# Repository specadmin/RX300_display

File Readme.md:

# Lexus RX300 LCD Display with Rear/Side Cameras View and Multimedia Support #

This project is an LCD display for Lexus RX300 (1998...2003). It is beeing built in order to replace the standard "blue" display in Lexus RX300 and Toyota Harrier.

<div align="center">  </div>
<div align="center">  </div>

----

For now this project has:

+ a complete integration with vehicle's MPX bus;
+ a complete integration with climate control and trip computer;
+ up to three analog cameras support (composite input);
+ close-to-original display view (any view can be built);
+ real time clock.

The following tasks are in progress:

* on-board player support (amplifier, radio and CD-player);
* migrating to ARM STM32 platform.

The following features could be implemented in future:

* HDMI input for Android-stick;
* independent media center with full-band radio and MP3 support.

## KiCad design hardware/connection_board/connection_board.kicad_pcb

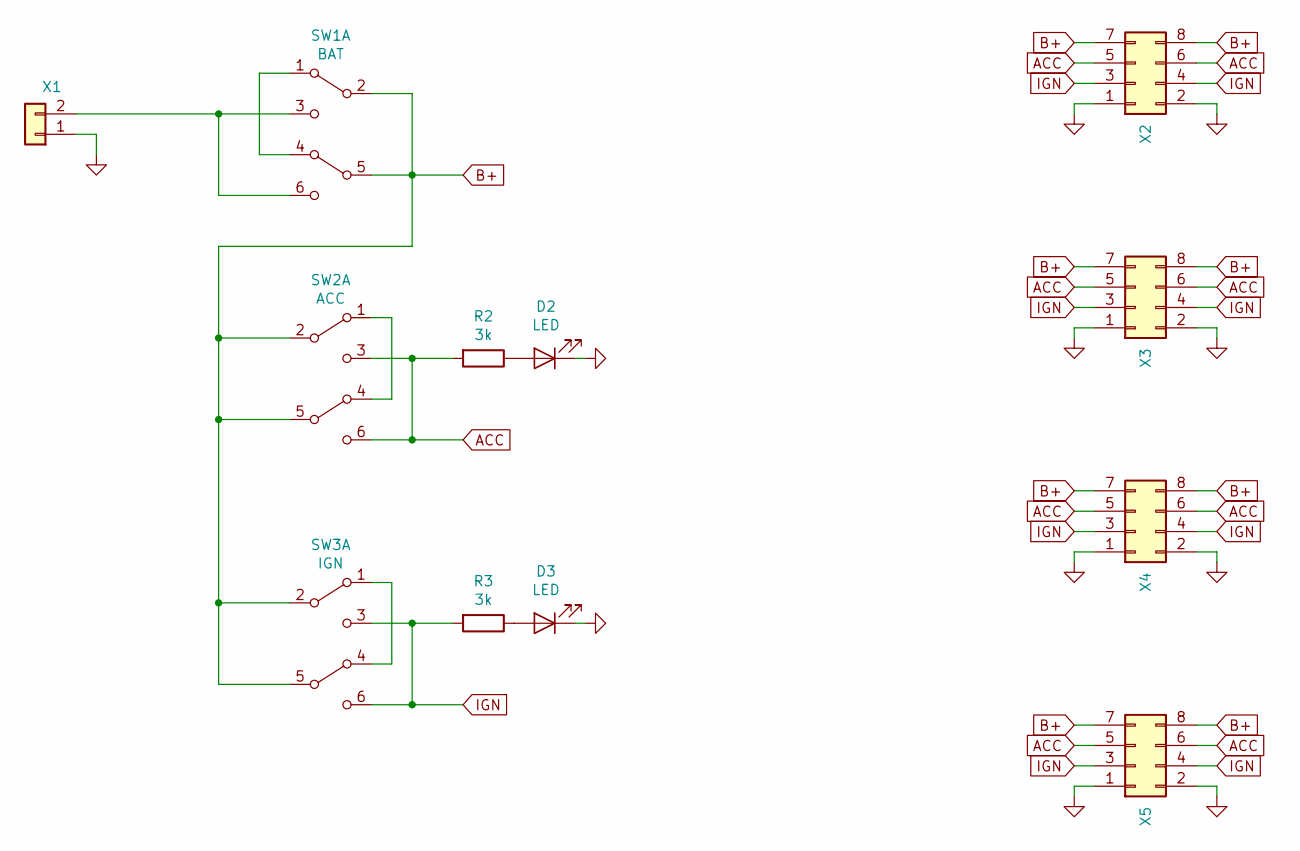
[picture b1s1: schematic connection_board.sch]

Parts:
D2, D3: LED; LED_D3.0mm
R2, R3: 3k; R_0805_2012Metric
SW1: BAT; Switch_2x03
SW2: ACC; Switch_2x03
SW3: IGN; Switch_2x03
X1: Conn_01x02; PinHeader_1x02_P2.54mm_Horizontal
X2, X3, X4, X5: Conn_02x04_Odd_Even; PinHeader_2x04_P2.54mm_Horizontal

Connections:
ACC: R2.2, SW2.3 (C), SW2.6 (C), X2.5, X2.6, X3.5, X3.6, X4.5, X4.6, X5.5, X5.6
B+: SW1.2 (B), SW1.5 (B), SW2.2 (B), SW2.5 (B), SW3.2 (B), SW3.5 (B), X2.7, X2.8, X3.7, X3.8, X4.7, X4.8, X5.7, X5.8
GND: D2.1 (K), D3.1 (K), X1.1, X2.1, X2.2, X3.1, X3.2, X4.1, X4.2, X5.1, X5.2
IGN: R3.2, SW3.3 (C), SW3.6 (C), X2.3, X2.4, X3.3, X3.4, X4.3, X4.4, X5.3, X5.4
unnamed: D2.2 (A), R2.1
unnamed: D3.2 (A), R3.1
unnamed: SW1.1 (A), SW1.4 (A)
unnamed: SW1.3 (C), SW1.6 (C), X1.2
unnamed: SW2.1 (A), SW2.4 (A)
unnamed: SW3.1 (A), SW3.4 (A)

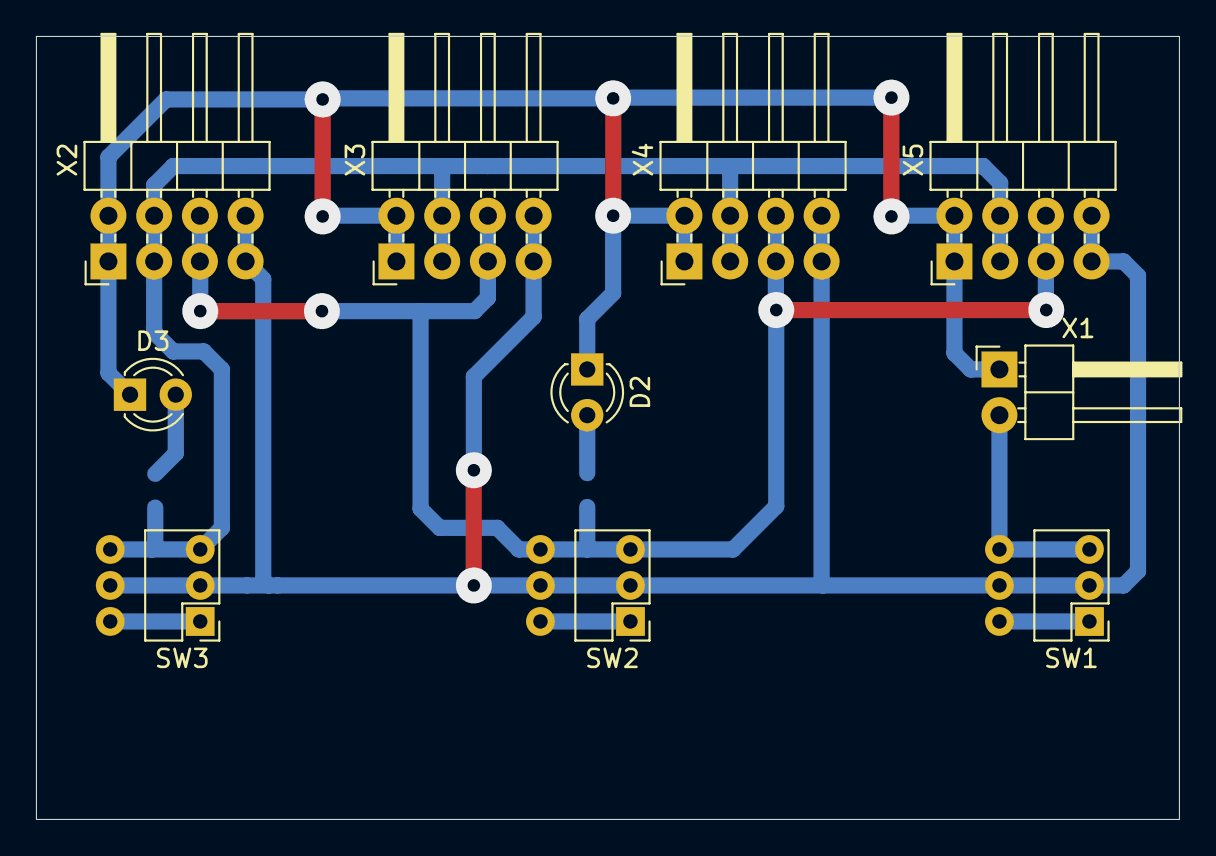
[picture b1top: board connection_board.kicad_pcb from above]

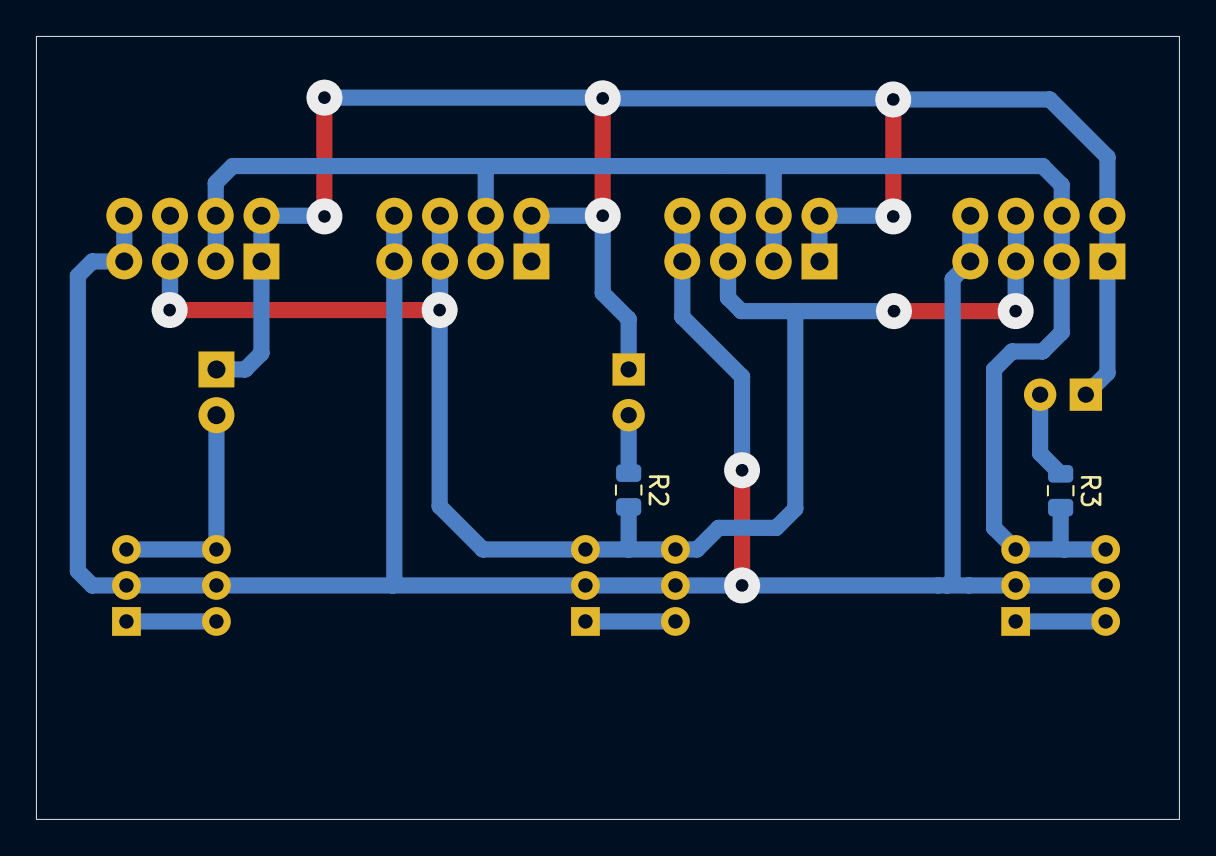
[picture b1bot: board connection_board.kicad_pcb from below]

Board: 2 copper layers, 63.5 x 43.5 mm, 12 parts (2 on the bottom side), 10 nets.

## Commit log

2020-01-12 Обновлены зависимости
2020-01-12 Актуализирован интерфейс с библиотекой
2020-01-12 Обновлена версия библиотеки
2020-01-13 Font gliphs reworked to left-side alignment
2020-01-18 Looks better by this way
2020-01-18 Crystal3 font implemented
2020-01-28 Реализован классический интерфейс
2020-02-08 Car drawings
2020-02-09 More crystal smbols
2020-02-10 Завершена отрисовка содержимого дисплея
2020-05-06 works
2020-05-27 RTD2660 library version updated
2020-05-27 AVR-misc library version updated
2020-05-27 AVR-debug library version updated
2020-05-27 A lot of changes
2020-05-27 Clock implementation
2020-05-27 Objects redistribution
2020-05-28 Trip computer implemented
2020-06-01 Trip comp updates
2020-06-26 Trip computer implemented completely
2020-06-26 Code beauty
2021-03-24 Rear camera implemented
2021-10-11 Rear camera view auto on/off
2021-10-11 Description added
